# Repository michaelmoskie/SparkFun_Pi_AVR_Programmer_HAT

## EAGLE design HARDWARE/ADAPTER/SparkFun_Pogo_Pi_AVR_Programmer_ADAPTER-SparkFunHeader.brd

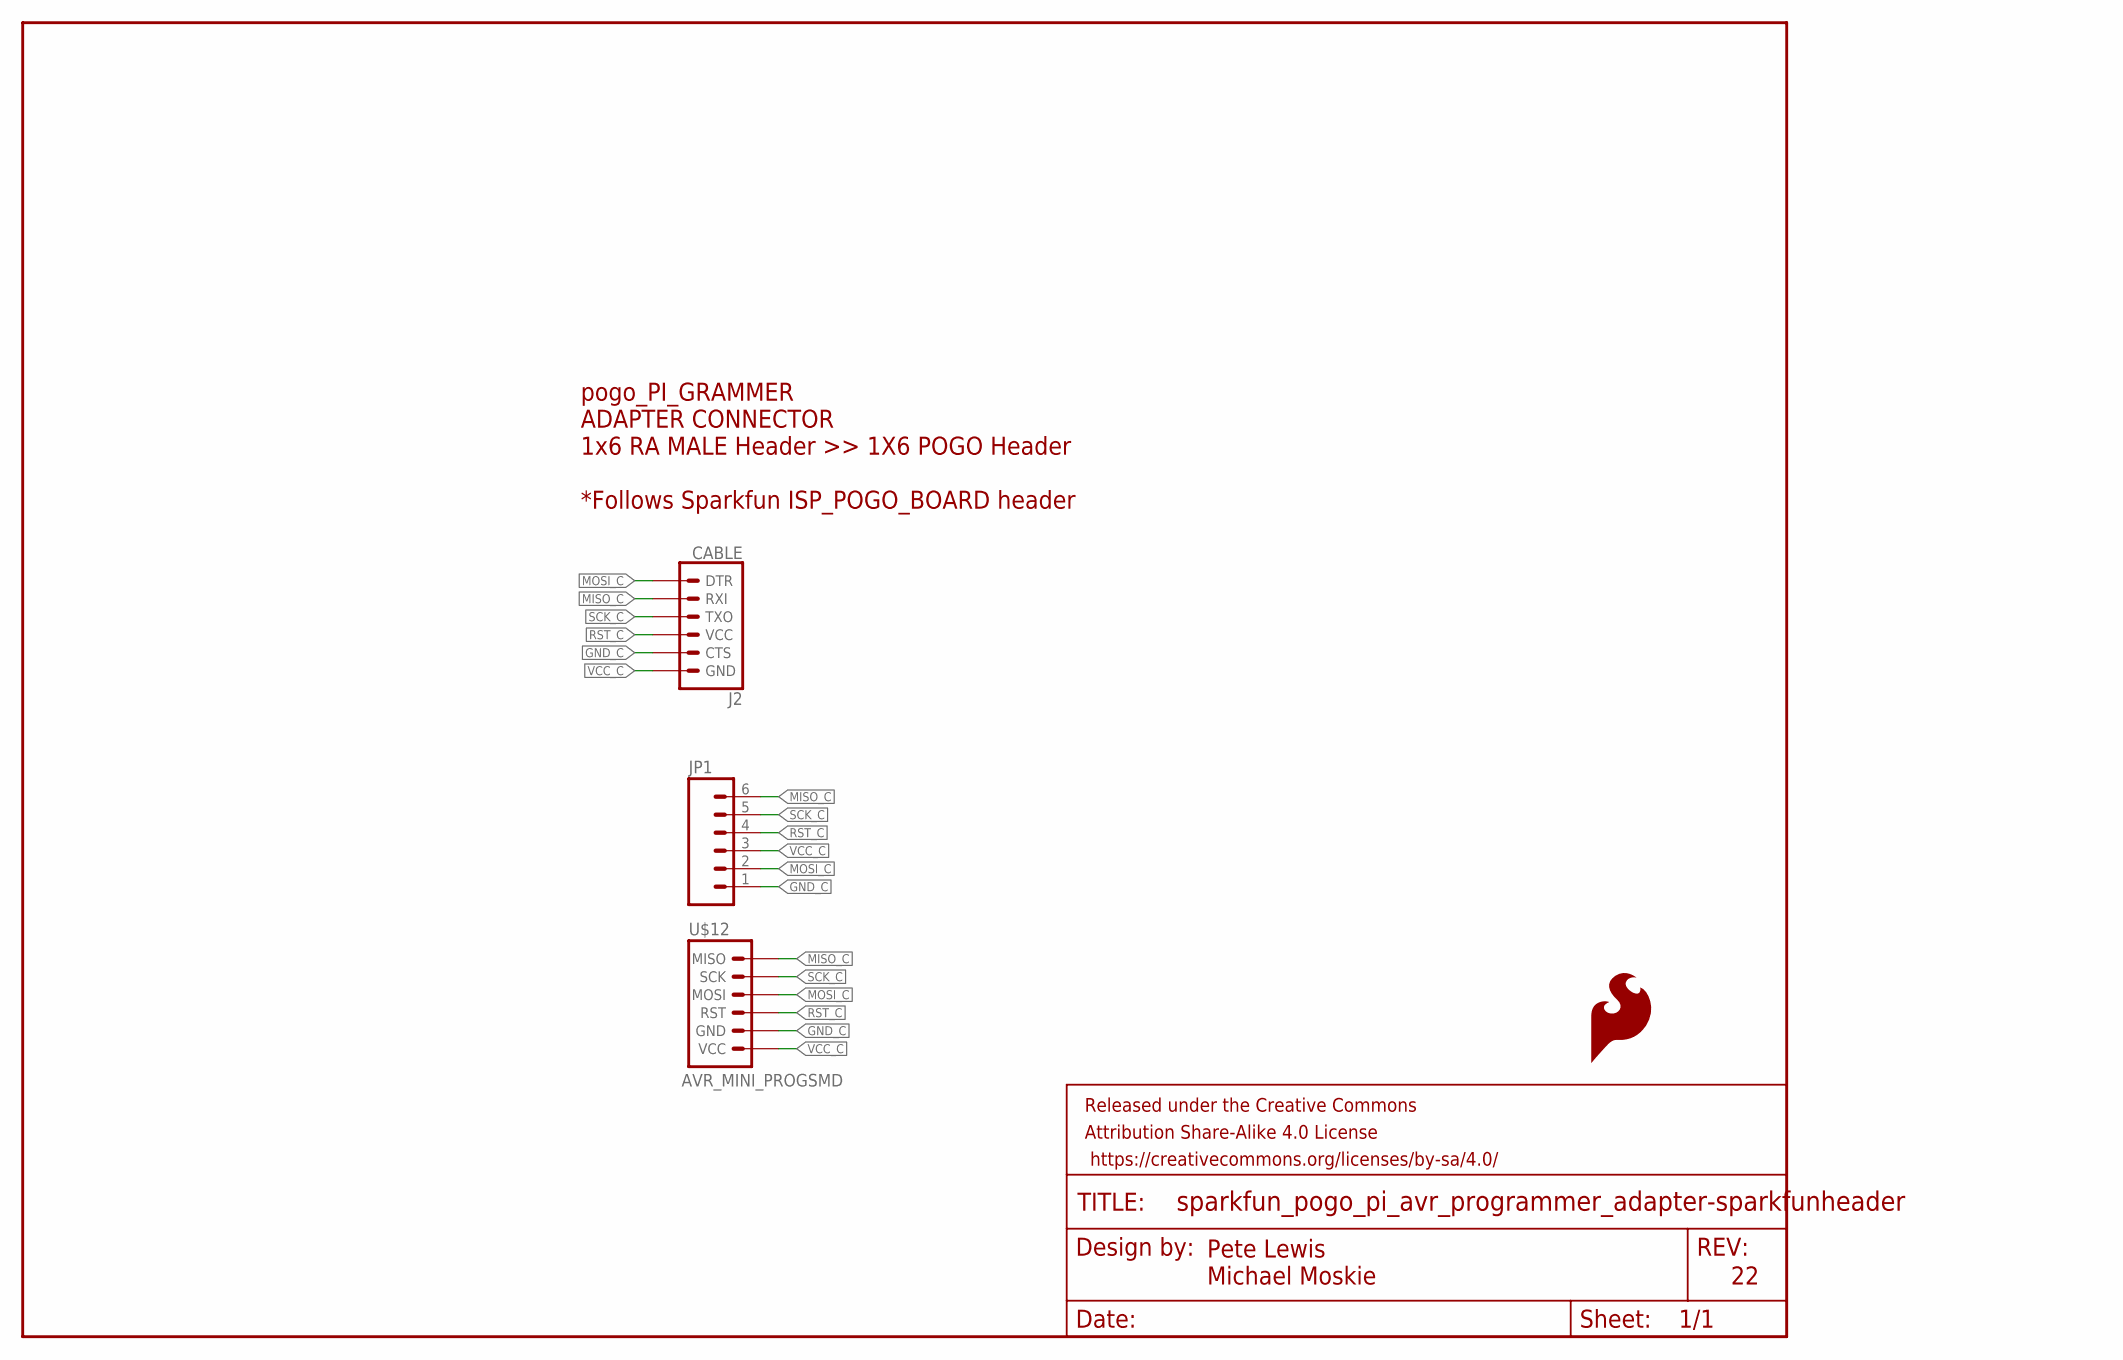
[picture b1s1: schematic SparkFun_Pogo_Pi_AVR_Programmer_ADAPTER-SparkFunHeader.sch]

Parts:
FRAME1: FRAME-LETTER; CREATIVE_COMMONS
J2: CABLE; 1X06-SMD_RA_MALE
JP1: M06POLAR; MOLEX-1X6
LOGO1: SFE_LOGO_FLAME.1_INCH; SFE_LOGO_FLAME_.1
U$12: AVR_MINI_PROGSMD; AVR_MINI_PROG

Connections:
GND_C: J2.5 (CTS), JP1.1, U$12.2 (GND)
MISO_C: J2.2 (RXI), JP1.6, U$12.6 (MISO)
MOSI_C: J2.1 (DTR), JP1.2, U$12.4 (MOSI)
RST_C: J2.4 (VCC), JP1.4, U$12.3 (RST)
SCK_C: J2.3 (TXO), JP1.5, U$12.5 (SCK)
VCC_C: J2.6 (GND), JP1.3, U$12.1 (VCC)

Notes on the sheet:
pogo_PI_GRAMMER ADAPTER CONNECTOR 1x6 RA MALE Header >> 1X6 POGO Header *Follows Sparkfun ISP_POGO_BOARD header
Pete Lewis Michael Moskie

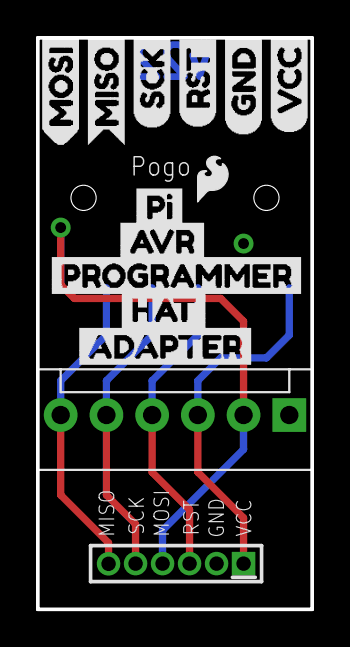
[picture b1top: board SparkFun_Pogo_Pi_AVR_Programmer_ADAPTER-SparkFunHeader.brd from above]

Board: 2 copper layers, 15.2 x 31.8 mm, 16 parts (1 on the bottom side), 6 nets.

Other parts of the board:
U$1: GND1
U$2: MISO5
U$3: MOSI4
U$4: RST2
U$5: SCK3
U$6: VCC0
U$7: PI0
U$8: AVR1
U$9: PROGRAMMER2
U$10: HAT3
U$11: ADAPTER4

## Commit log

2018-07-27 Added proper pogo header.

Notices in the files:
parts and their libraries:
SparkFun-Aesthetics: Licensing: CC v3.0 Share-Alike You are welcome to use this library for commercial purposes.
SparkFun-Aesthetics: Released under the Creative Commons Attribution Share-Alike 4.0 License
SparkFun-Aesthetics: https://creativecommons.org/licenses/by-sa/4.0
